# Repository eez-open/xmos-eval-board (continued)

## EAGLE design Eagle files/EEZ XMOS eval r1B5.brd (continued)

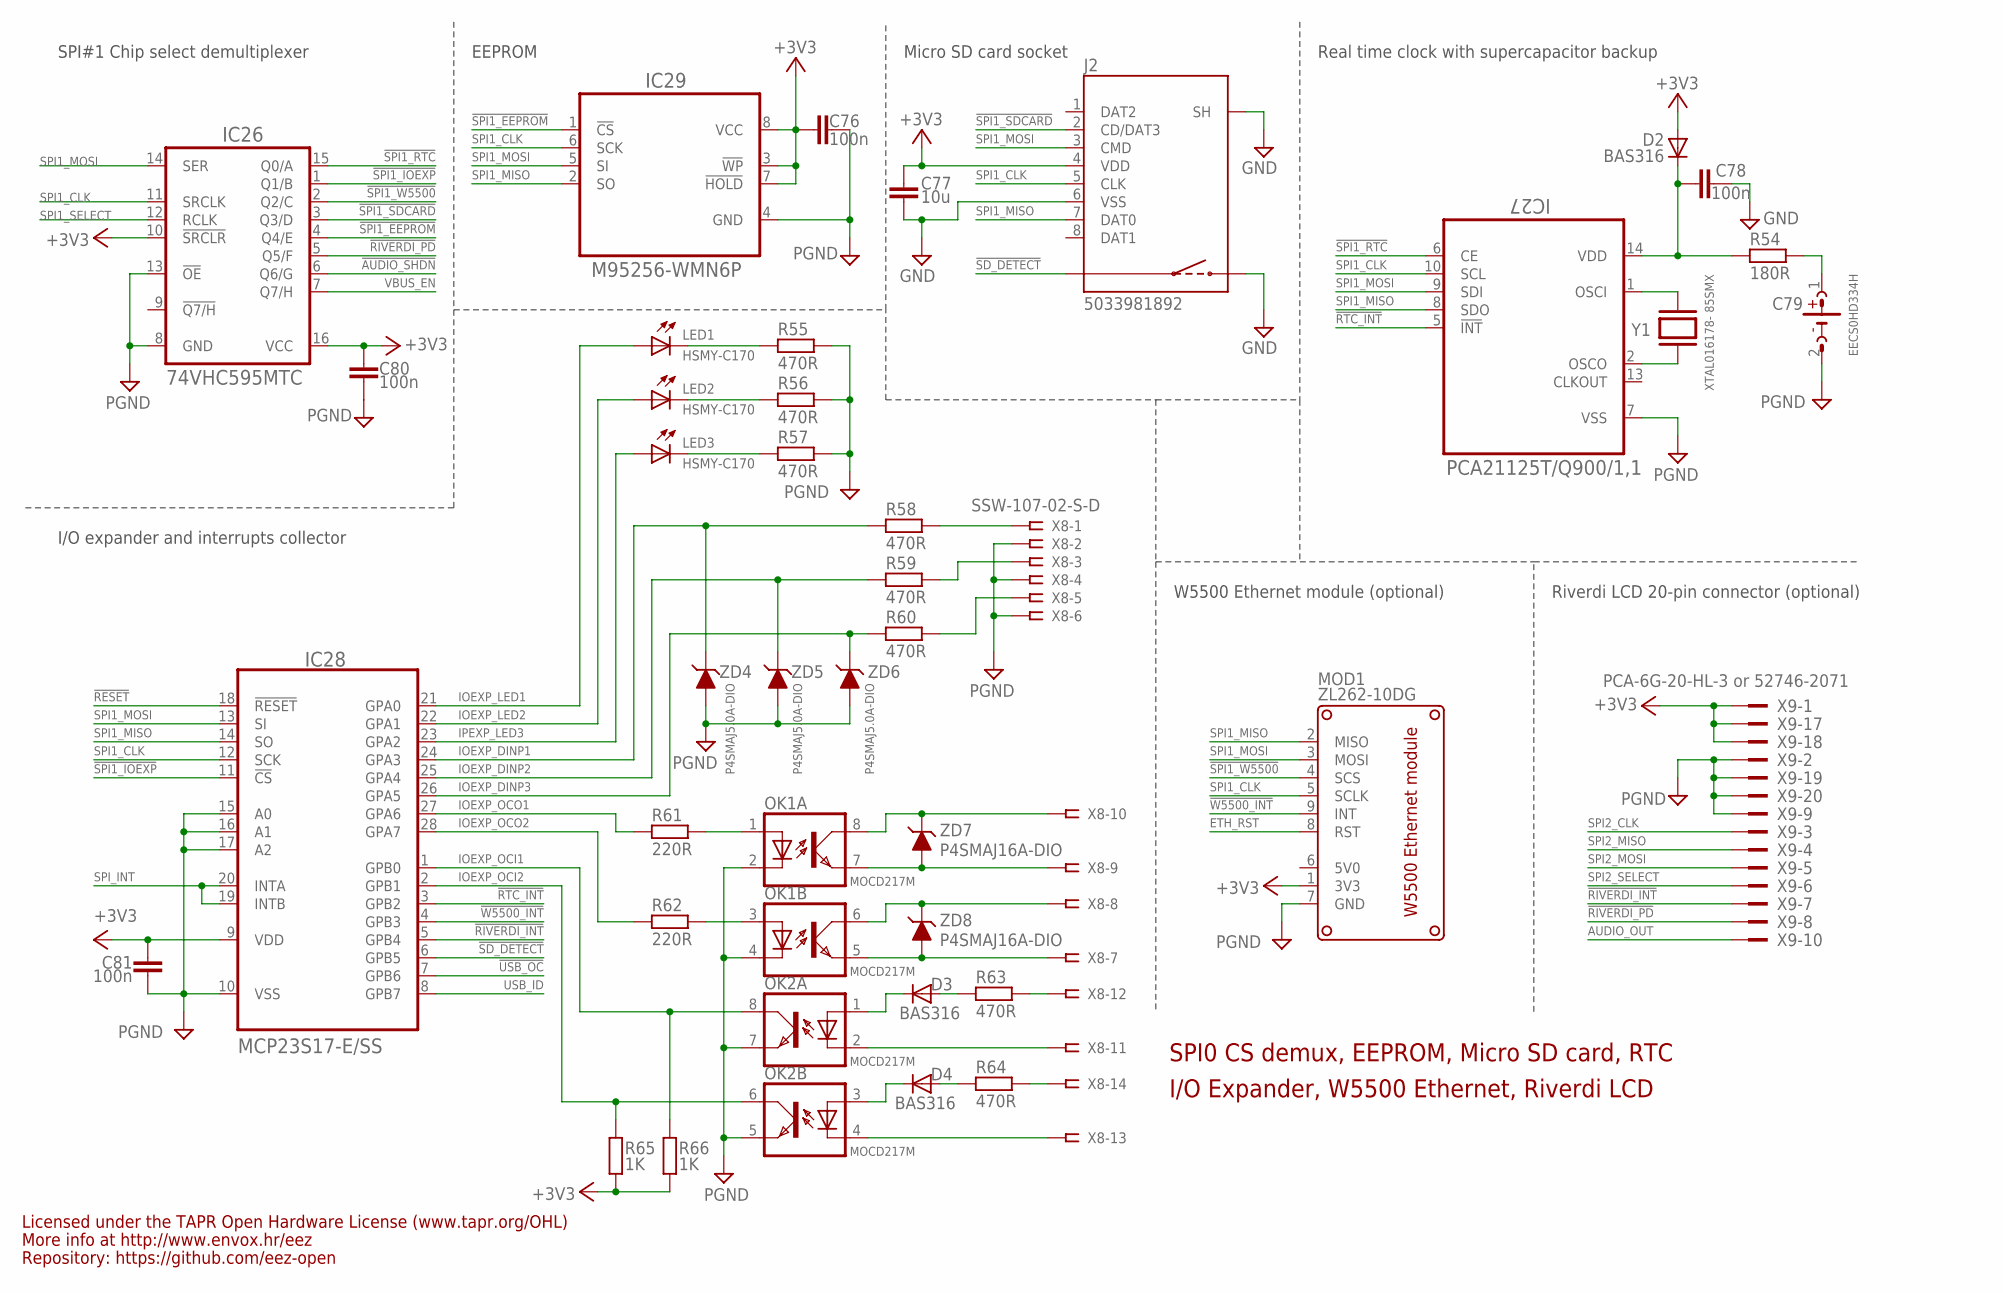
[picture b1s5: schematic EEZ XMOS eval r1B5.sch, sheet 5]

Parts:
C76, C78, C80, C81: 100n; C0603
C77: 10u; C1210
C79: EECS0HD334H; SG-R10MM
D2, D3, D4: BAS316; SOD323-W
IC26: 74VHC595MTC; PW(R-PDSO-G16)
IC27: PCA21125T/Q900/1,1; SOP65P640X120-14N
IC28: MCP23S17-E/SS; SOP65P780X200-28N
IC29: M95256-WMN6P; SOIC127P600X175-8N
J2: 5033981892
LED1, LED2, LED3: HSMY-C170; LED_0805
MOD1: ZL262-10DG; ETH_W5500_MODULE
OK1, OK2: MOCD217M; SO8-OPTO
R54: 180R; R0805
R55, R56, R57, R58, R59, R60, R63, R64: 470R; R0805
R61, R62: 220R; R0805
R65, R66: 1K; R0805
X8: SSW-107-02-S-D
X9: PCA-6G-20-HL-3 or 52746-2071; FPC-20_ROTATED
Y1: XTAL016178- 85SMX; 85SMX
ZD4, ZD5, ZD6: P4SMAJ5.0A-DIO; DO214AC
ZD7, ZD8: P4SMAJ16A-DIO; DO214AC

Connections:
5V0: MOD1.6 (5V0)
!AUDIO_SHDN: IC26.6 (Q6/G); also elsewhere on the board
!RESET: IC28.18 (!RESET); also elsewhere on the board
!RIVERDI_INT: IC28.5 (GPB4), X9.7
!RIVERDI_PD: IC26.5 (Q5/F), X9.8
!RTC_INT: IC27.5 (!INT), IC28.3 (GPB2)
!SD_DETECT: IC28.6 (GPB5), J2.SW1
!SPI1_EEPROM: IC26.4 (Q4/E), IC29.1 (!CS)
!SPI1_IOEXP: IC26.1 (Q1/B), IC28.11 (!CS)
!SPI1_RTC: IC26.15 (Q0/A), IC27.6 (CE)
!SPI1_SDCARD: IC26.3 (Q3/D), J2.2 (CD/DAT3)
!SPI1_W5500: IC26.2 (Q2/C), MOD1.4 (SCS)
!USB_OC: IC28.7 (GPB6); also elsewhere on the board
!W5500_INT: IC28.4 (GPB3), MOD1.9 (INT)
+3V3: C76.1, C77.1, C80.2, C81.1, D2.A, IC26.10 (!SRCLR), IC26.16 (VCC), IC28.9 (VDD), IC29.3 (!WP), IC29.7 (!HOLD), IC29.8 (VCC), J2.4 (VDD), MOD1.1 (3V3), R65.2, R66.2, X9.1, X9.17, X9.18; also elsewhere on the board
AUDIO_OUT: X9.10; also elsewhere on the board
ETH_RST: MOD1.8 (RST); also elsewhere on the board
GND: C76.2, C77.2, C78.1, C79.2 (-), C80.1, C81.2, IC26.8 (GND), IC26.13 (!OE), IC27.7 (VSS), IC28.10 (VSS), IC28.15 (A0), IC28.16 (A1), IC28.17 (A2), IC29.4 (GND), J2.6 (VSS), J2.S (SH), J2.SW2, MOD1.7 (GND), OK1.2 (C), OK1.4 (C), OK2.5 (EMIT), OK2.7 (EMIT), R55.1, R56.1, R57.1, X8.2, X8.4, X8.6, X9.2, X9.9, X9.19, X9.20, ZD4.A, ZD5.A, ZD6.A; also elsewhere on the board
IOEXP_DINP1: IC28.24 (GPA3), R58.2, ZD4.C
IOEXP_DINP2: IC28.25 (GPA4), R59.2, ZD5.C
IOEXP_DINP3: IC28.26 (GPA5), R60.2, ZD6.C
IOEXP_LED1: IC28.21 (GPA0), LED1.A
IOEXP_LED2: IC28.22 (GPA1), LED2.A
IOEXP_OCI1: IC28.1 (GPB0), OK2.8 (COL), R66.1
IOEXP_OCI2: IC28.2 (GPB1), OK2.6 (COL), R65.1
IOEXP_OCO1: IC28.27 (GPA6), R61.2
IOEXP_OCO2: IC28.28 (GPA7), R62.2
IPEXP_LED3: IC28.23 (GPA2), LED3.A
unnamed: OK2.4 (C), X8.13
unnamed: OK1.8 (COL), X8.10, ZD7.C
unnamed: OK1.7 (EMIT), X8.9, ZD7.A
unnamed: OK1.6 (COL), X8.8, ZD8.C
unnamed: OK1.5 (EMIT), X8.7, ZD8.A
unnamed: OK1.1 (A), R61.1
unnamed: D3.C, OK2.1 (A)
unnamed: OK2.2 (C), X8.11
unnamed: D3.A, R63.2
unnamed: IC27.1 (OSCI), Y1.1
unnamed: D4.A, R64.2
unnamed: D4.C, OK2.3 (A)
unnamed: R64.1, X8.14
unnamed: OK1.3 (A), R62.1
unnamed: R63.1, X8.12
unnamed: IC27.2 (OSCO), Y1.4 (2)
unnamed: LED1.C, R55.2
unnamed: LED2.C, R56.2
unnamed: LED3.C, R57.2
unnamed: R58.1, X8.1
unnamed: R59.1, X8.3
unnamed: R60.1, X8.5
unnamed: C79.1 (+), R54.1
unnamed: C78.2, D2.C, IC27.14 (VDD), R54.2
SPI1_CLK: IC26.11 (SRCLK), IC27.10 (SCL), IC28.12 (SCK), IC29.6 (SCK), J2.5 (CLK), MOD1.5 (SCLK); also elsewhere on the board
SPI1_MISO: IC27.8 (SDO), IC28.14 (SO), IC29.2 (SO), J2.7 (DAT0), MOD1.2 (MISO); also elsewhere on the board
SPI1_MOSI: IC26.14 (SER), IC27.9 (SDI), IC28.13 (SI), IC29.5 (SI), J2.3 (CMD), MOD1.3 (MOSI); also elsewhere on the board
SPI1_SELECT: IC26.12 (RCLK); also elsewhere on the board
SPI2_CLK: X9.3; also elsewhere on the board
SPI2_MISO: X9.4; also elsewhere on the board
SPI2_MOSI: X9.5; also elsewhere on the board
SPI2_SELECT: X9.6; also elsewhere on the board
SPI_INT: IC28.19 (INTB), IC28.20 (INTA); also elsewhere on the board
USB_ID: IC28.8 (GPB7); also elsewhere on the board
VBUS_EN: IC26.7 (Q7/H); also elsewhere on the board

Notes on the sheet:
Licensed under the TAPR Open Hardware License (www.tapr.org/OHL)
Repository: https://github.com/eez-open
More info at http://www.envox.hr/eez
SPI0 CS demux, EEPROM, Micro SD card, RTC
Riverdi LCD 20-pin connector (optional)
Real time clock with supercapacitor backup
W5500 Ethernet module (optional)
SPI#1 Chip select demultiplexer
I/O expander and interrupts collector
I/O Expander, W5500 Ethernet, Riverdi LCD
Micro SD card socket
EEPROM

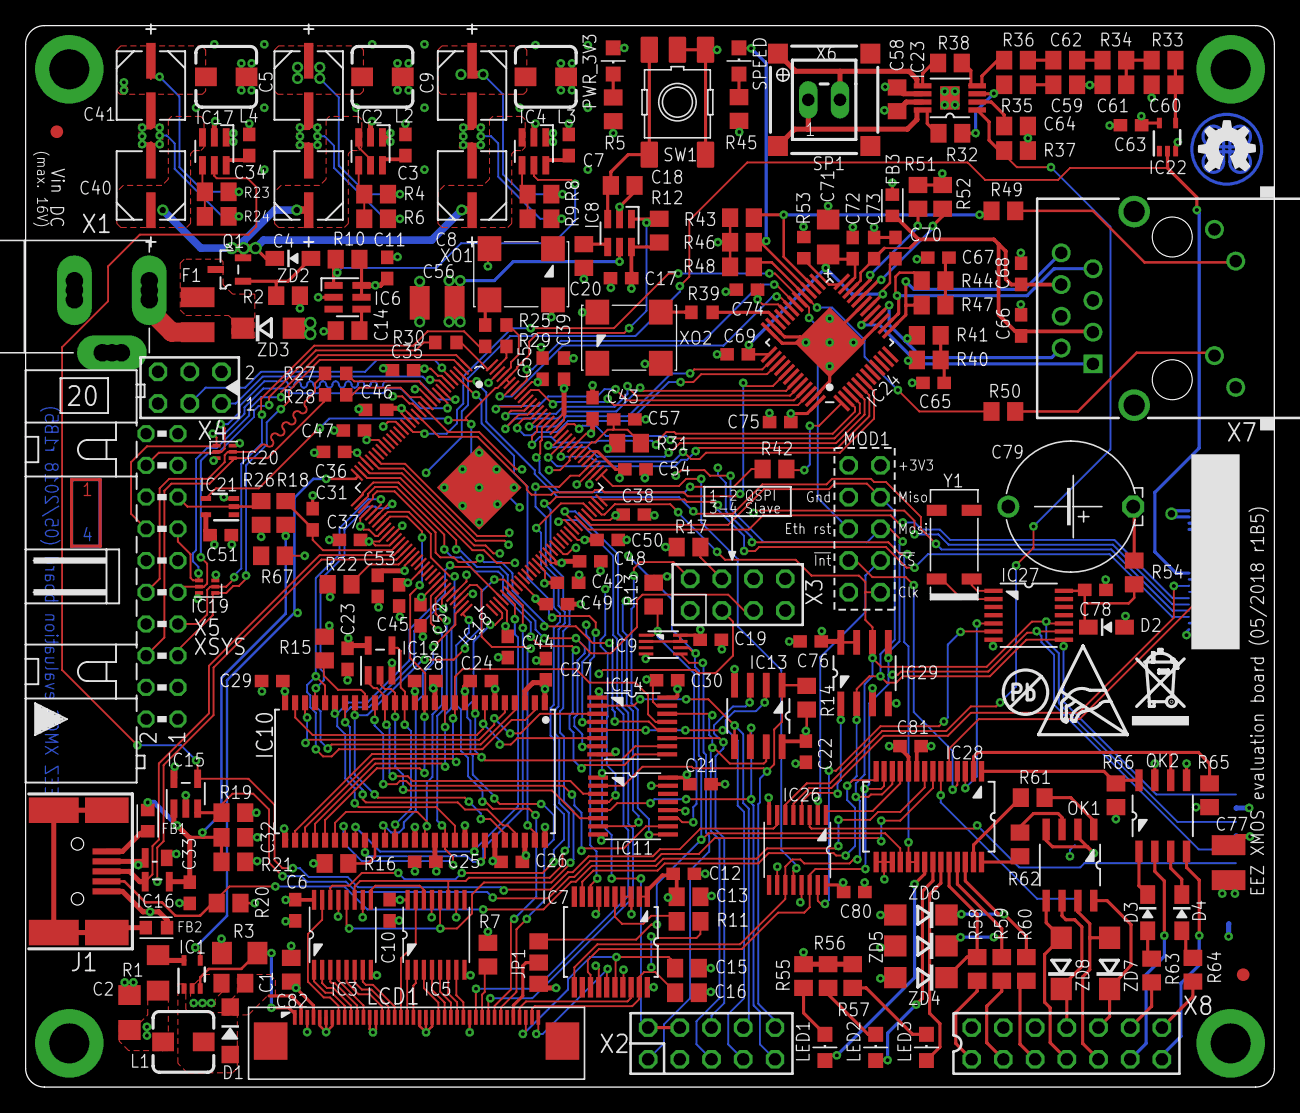
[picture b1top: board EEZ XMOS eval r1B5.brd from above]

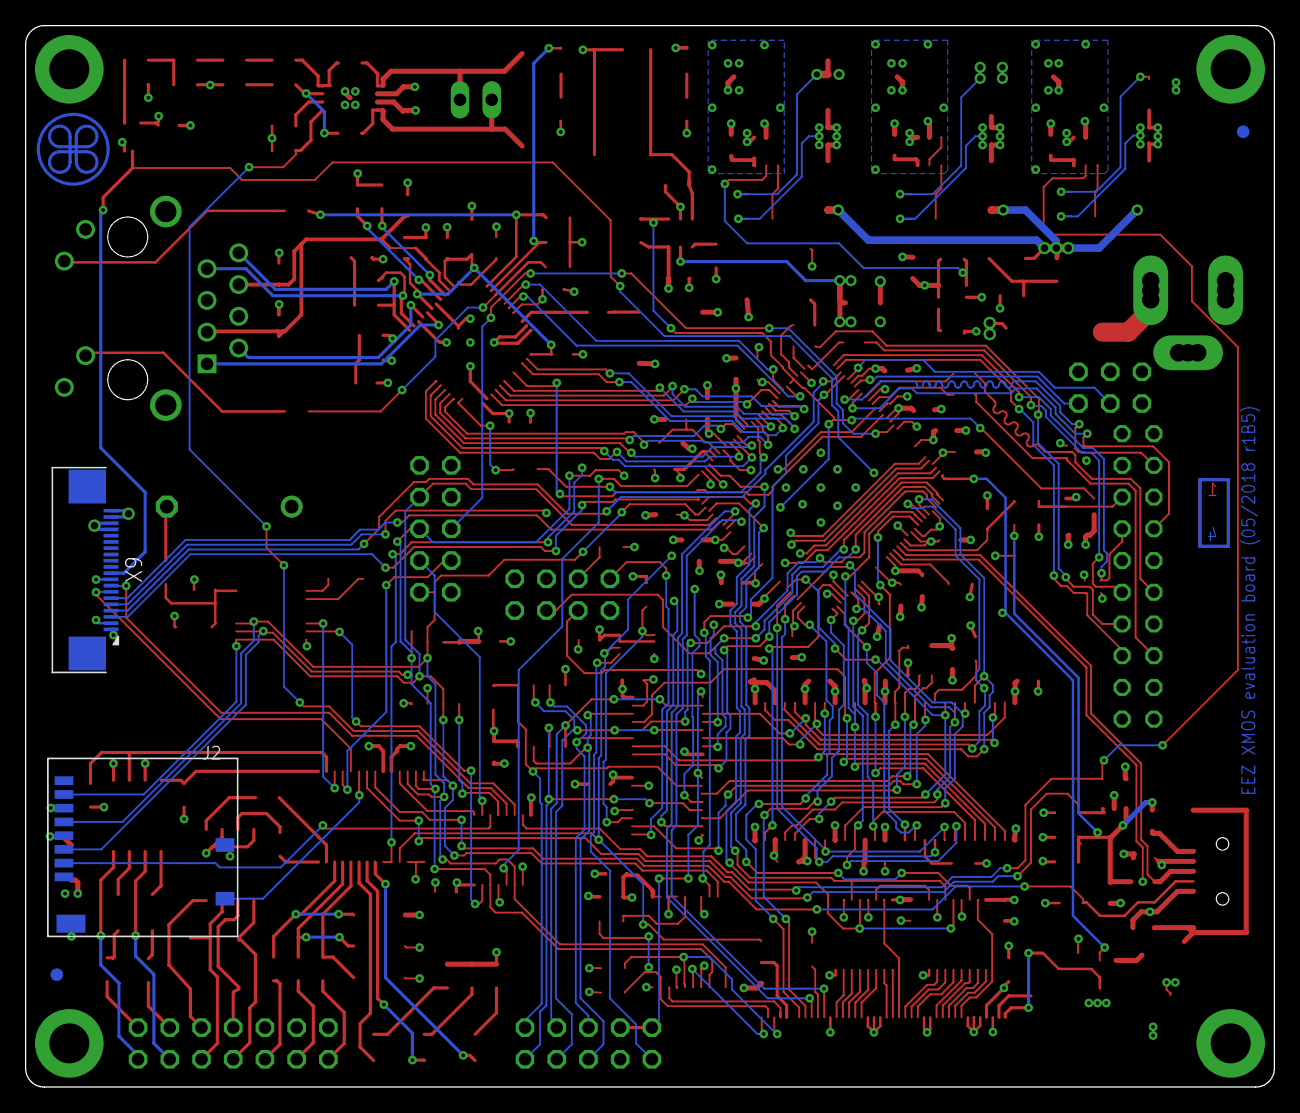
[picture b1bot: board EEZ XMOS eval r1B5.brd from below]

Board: 4 copper layers, 100.0 x 85.0 mm, 229 parts (3 on the bottom side), 231 nets.

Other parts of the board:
EEZ_SIGNATURE: SIGNATURESMALL; SIGNATURE_5MM
U$1: RECYCLE_BIN1/8
U$5: PB_SMALL
U$6: ESD_SYMBOL

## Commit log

2018-01-21 first commit, BOM is missing
2018-01-21 portmap filename change
2018-01-21 pin swap on X3
2018-01-22 BOM first version, added R67 as test point
2018-01-27 .brd file optimization
2018-02-24 #1, #2
2018-03-07 fixed flash memory model
2018-03-14 memory flashing example
2018-05-03 better placement of SD card capacitor (C77)
